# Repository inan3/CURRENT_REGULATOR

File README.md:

PCB Module based on STM32G491RET6 acting as a water sensor just for tests purposes. Nominal working voltage is 12V.
It is designed to receive commands either by UART or LIN-BUS containing info about:
  1. How many voltage between 0-3.3V to put in a connector A. 
     DAC_OUT1 from the STM32 is used for this purpose.
  2. How many current between 0-20mA to put in a connector B.
     DAC_OUT2 from the STM32 is used for this purpose. An equivalent voltage is generated from the DAC that will go through a phase of voltage-current conversion with the Improved Howland Current Pump achieving an outside current from 0mA to 20mA with 0V-3.3V.
  3. Toggle between 0V & 12V that must reach a connector C.
     This phase is achieved with high side switching topology to toggle 4 different pins of 2 separate connectores to toggle between 0V and 12V.

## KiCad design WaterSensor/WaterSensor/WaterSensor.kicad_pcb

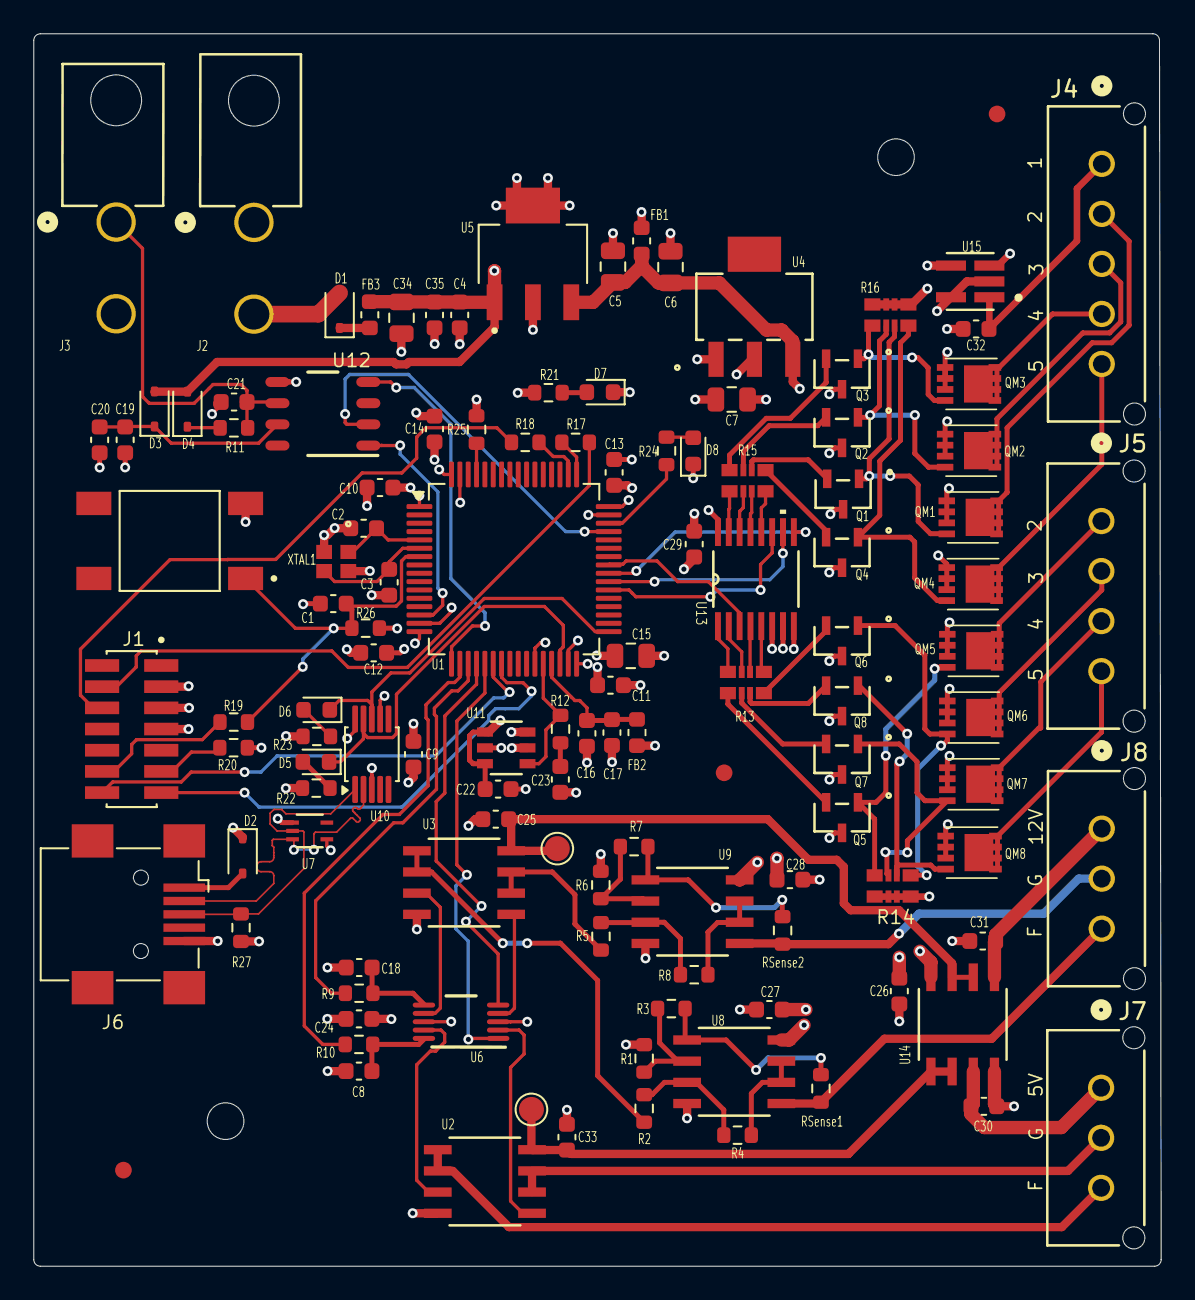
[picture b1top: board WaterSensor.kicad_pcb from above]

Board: 4 copper layers, 67.6 x 73.9 mm, 123 parts (0 on the bottom side), 104 nets.

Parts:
C1, C24, C25, C26, C27, C28, C29, C30, C31, C32, C33: 0.1uF; C_0603_1608Metric
C2, C3: 8.2pF; C_0603_1608Metric
C4: 0.22uF; C_0603_1608Metric
C5, C6, C7, C34: 10uF; C_0805_2012Metric
C8, C18: 10nF; C_0603_1608Metric
C9, C17, C20: 1uF; C_0603_1608Metric
C10, C11, C12, C13, C14, C16, C19, C35: 100nF; C_0603_1608Metric
C15: 4.7uF; C_0805_2012Metric
C21: 1nF; C_0603_1608Metric
C22, C23: 2.2uF; C_0603_1608Metric
D1, D2, D3, D4: 1N5819WS; D_SOD-323
D5: Yellow; LED_0603_1608Metric
D6: Green; LED_0603_1608Metric
D7: Red; LED_0603_1608Metric
D8: Blue; LED_0603_1608Metric
FB1, FB3: HI1206N101R-10; L_0603_1608Metric
FB2: HZ0603C601R-10; L_0603_1608Metric
FID1, FID2, FID3: Fiducial; Fiducial_1mm_Mask2mm
H1, H2: MountingHole; MountingHole_2.2mm_M2
J1: ST-LINK; Connector_IDC_02x07_1_27mm_SMD
J2: PS_IN; Conn_1x2_MiniFit_1724480002
J3: LIN; Conn_1x2_MiniFit_1724480002
J4: BLK8C; Conn_1x5_MicroFit_436500527
J5: BLK9C; Conn_1x4_MicroFit_0436500427
J6: USB_B_Mini; USB_Mini-B_Wuerth_65100516121_Horizontal
J7: BLKA; Conn_1x3_MicroFit_436500327
J8: BLKB; Conn_1x3_MicroFit_436500327
Q1, Q2, Q3, Q4, Q5, Q6, Q7, Q8: BC848BLT1G; SOT-23_ONS-L
QM1, QM2, QM3, QM4, QM5, QM6, QM7, QM8: PMOS; LIB-SIS862DNT1GE3
R1, R2, R3, R4, R5, R6, R7, R8: 100k; R_0603_1608Metric
R9, R10, R11: 1k; R_0603_1608Metric
R12: 50; R_0603_1608Metric
R13, R14, R15, R16: EXB-28V220JX; EXB28V_PAN
R17, R18, R19: 22; R_0603_1608Metric
R20: 100; R_0603_1608Metric
R21, R22: 220; R_0603_1608Metric
R23, R24: 120; R_0603_1608Metric
R25, R26: 10k; R_0603_1608Metric
R27: 1k5; R_0603_1608Metric
RSense1, RSense2: 165; R_0603_1608Metric
SW1: SW_Push; SW_TS04-66-43-BK-160-SMT
TP1: TP1; TestPoint_Pad_D1.5mm
TP2: TP2; TestPoint_Pad_D1.5mm
U1: STM32G491RET6; LQFP-64_10x10mm_P0.5mm
U2, U3, U8, U9, U14: OPA2990IDR; D8_TEX-M
U4: LM1117MP-3.3; SOT223-318H_OSI-M
U5: LM7805MPX/NOPB; LM7805MPX_NOPB
U6: TS5A23157QDGSRQ1; DGS0010A_N
U7: TPD2E001DRLR; DRL5-M
U10: CH340E; MSOP-10_3x3mm_P0.5mm
U11: MCP1501T-33E/CHY; SOT-23-6_CHY_MCH
U12: TLIN1029DRQ1; D0008A_N
U13: SN74LV4051APWR; PW16
U15: OPA990IDBVR; DBV0005A-IPC_A
XTAL1: FA-128 24.0000MB-W0; FA-128_2x1p6_SEC

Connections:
+3.3V: C7.1, C9.1, C10.1, C11.1, C12.1, C13.1, C14.1, C15.1, C22.1, C29.1, FB2.1, J1.3, R21.1, R22.1, R23.1, R26.1, R27.1, U1.1 (VBAT), U1.16 (VDD), U1.32 (VDD), U1.48 (VDD), U1.64 (VDD), U4.2 (VO), U10.7 (VCC), U10.10 (V3), U11.4 (*SHDN), U11.6 (VDD), U13.16 (VCC)
+5V: C5.1, C6.1, C24.1, FB1.2, U4.3 (VI), U5.3 (OUTPUT), U6.8 (V+), U7.4 (VCC)
+12V: QM1.3 (S), QM2.3 (S), QM3.3 (S), QM4.3 (S), QM5.3 (S), QM6.3 (S), QM7.3 (S), QM8.3 (S), R14.5, R14.6, R14.7, R14.8, R16.5, R16.6, R16.7, R16.8, U15.2 (-), U15.5
/BLK-C-Water/+12V_BLK8C-2: J4.2, QM1.1 (D)
/BLK-C-Water/+12V_BLK8C-3: J4.3, QM2.1 (D)
/BLK-C-Water/+12V_BLK8C-4: J4.4, QM3.1 (D)
/BLK-C-Water/+12V_BLK8C-5: J4.5, QM4.1 (D)
/BLK-C-Water/+12V_BLK9C-2: J5.1, QM5.1 (D)
/BLK-C-Water/+12V_BLK9C-3: J5.2, QM6.1 (D)
/BLK-C-Water/+12V_BLK9C-4: J5.3, QM7.1 (D)
/BLK-C-Water/+12V_BLK9C-5: J5.4, QM8.1 (D)
/BLK-C-Water/BLKC_PWR: C32.1, J4.1, U15.1 (+)
/DAC_PROT&SWITCH/BLKA_PWR: C30.1, J7.1, U14.3 (In1+)
/DAC_PROT&SWITCH/BLKA_PWR_BUFF: C33.1, TP1.1, U2.8 (VCC+), U14.1 (Out1), U14.2 (In1-)
/DAC_PROT&SWITCH/BLKB_PWR: C31.1, J8.1, U14.5 (In2+)
/DAC_PROT&SWITCH/BLKB_PWR_BUFF: C25.1, TP2.1, U3.8 (VCC+), U14.6 (In2-), U14.7 (Out2)
/DAC_PROT&SWITCH/DAC_A_IN1+: U2.3 (In1+), U6.9 (NC1)
/DAC_PROT&SWITCH/DAC_A_IN2+: U2.5 (In2+), U6.2 (NO1)
/DAC_PROT&SWITCH/DAC_A_RAW_F: C8.2, R10.2, U6.10 (COM1)
/DAC_PROT&SWITCH/DAC_B_IN1+: U3.3 (In1+), U6.7 (NC2)
/DAC_PROT&SWITCH/DAC_B_IN2+: U3.5 (In2+), U6.4 (NO2)
/DAC_PROT&SWITCH/DAC_B_RAW_F: C18.1, R9.2, U6.6 (COM2)
/DAC_PROT&SWITCH/FW_DAC_IN_A: J7.3, U2.1 (Out1), U2.2 (In1-)
/DAC_PROT&SWITCH/GW_DAC_IN_A: J7.2, U2.6 (In2-), U2.7 (Out2)
/LIN_BUS: C21.1, J3.1, R11.2, U12.6 (LIN)
/USB_D+: J6.3 (D+), R27.2, U7.2 (IO1), U10.1 (UD+)
/USB_D-: J6.2 (D-), U7.3 (IO2), U10.2 (UD-)
/VIConverter/FW_DAC_IN_B_IN1-: R1.2, R3.1, U8.2 (In1-)
/VIConverter/FW_OUT2: R4.1, U8.6 (In2-), U8.7 (Out2)
/VIConverter/GW_DAC_IN_B_IN1-: R6.2, R7.1, U9.2 (In1-)
/VIConverter/GW_OUT2: R8.1, U9.6 (In2-), U9.7 (Out2)
/VIConverter/IoutFW: J8.3, RSense1.1, U8.5 (In2+)
/VIConverter/IoutGW: J8.2, RSense2.1, U9.5 (In2+)
BLKC_CTRL_IN: U1.41 (PC9), U13.3 (COM)
BLKC_SEL_A: U1.38 (PC6), U13.11 (A)
BLKC_SEL_B: U1.39 (PC7), U13.10 (B)
BLKC_SEL_C: U1.40 (PC8), U13.9 (C)
BOOT: R25.1, U1.61 (PB8)
DAC_IN_A: R10.1, U1.18 (PA4)
DAC_IN_B: R9.1, U1.19 (PA5)
EN_LIN: U1.45 (PA11), U12.2 (EN)
FW_DAC_IN_B: R2.1, U3.1 (Out1), U3.2 (In1-)
GND: C1.2, C2.2, C3.2, C4.2, C5.2, C6.2, C7.2, C8.1, C9.2, C10.2, C11.2, C12.2, C13.2, C14.2, C15.2, C16.2, C17.2, C18.2, C19.2, C20.2, C21.2, C22.2, C23.2, C24.2, C25.2, C26.2, C27.2, C28.2, C29.2, C30.2, C31.2, C32.2, C33.2, C34.2, C35.2, D7.1 (K), D8.1 (K), J1.5, J1.7, J2.1, J3.2, J6.5 (GND), Q1.3 (E), Q2.3 (E), Q3.3 (E), Q4.3 (E), Q5.3 (E), Q6.3 (E), Q7.3 (E), Q8.3 (E), R1.1, R6.1, R20.1, R25.2, SW1.2, U1.15 (VSS), U1.27 (VSSA), U1.31 (VSS), U1.47 (VSS), U1.63 (VSS), U2.4 (VCC-), U3.4 (VCC-), U4.1 (GND), U5.2 (GND), U5.4 (GND), U6.3 (GND), U7.1 (GND), U8.4 (VCC-), U9.4 (VCC-), U10.3 (GND), U11.2 (GND), U11.3 (GND), U11.5 (GND), U12.5 (GND), U13.6 (INH), U13.7 (GND), U13.8 (GND), U14.4 (VCC-), U15.4 (V-), XTAL1.2, XTAL1.4
GW_DAC_IN_B: R5.1, U3.6 (In2-), U3.7 (Out2)
IN_A: U1.21 (PA7), U6.1 (IN1)
IN_B: U1.20 (PA6), U6.5 (IN2)
In1+: R2.2, R4.2, U8.3 (In1+)
NRST: C1.1, R19.2, R26.2, SW1.1, U1.7 (PG10)
unnamed: C23.1, R12.2
unnamed: D1.1 (K), FB3.1
unnamed: D2.2 (A), J6.1 (VBUS)
unnamed: C19.1, C20.1, D3.1 (K), U12.7 (VSUP)
unnamed: D4.1 (K), R11.1
unnamed: D5.2 (A), R22.2
unnamed: D6.2 (A), R23.2
unnamed: D7.2 (A), R21.2
unnamed: D8.2 (A), R24.2
unnamed: J1.4, R17.1
unnamed: J1.6, R18.1
unnamed: J1.11, R20.2
unnamed: J1.12, R19.1
unnamed: Q1.2 (B), R15.6
unnamed: Q1.1 (C), QM1.2 (G), R16.3
unnamed: Q2.2 (B), R15.7
unnamed: Q2.1 (C), QM2.2 (G), R16.2
unnamed: Q3.2 (B), R15.8
unnamed: Q3.1 (C), QM3.2 (G), R16.1
unnamed: Q4.2 (B), R15.5
unnamed: Q4.1 (C), QM4.2 (G), R16.4
unnamed: Q5.2 (B), R13.5
unnamed: Q5.1 (C), QM5.2 (G), R14.4
unnamed: Q6.2 (B), R13.8
unnamed: Q6.1 (C), QM6.2 (G), R14.1
unnamed: Q7.2 (B), R13.6
unnamed: Q7.1 (C), QM7.2 (G), R14.3
unnamed: Q8.2 (B), R13.7
unnamed: Q8.1 (C), QM8.2 (G), R14.2
unnamed: R15.3, U13.13 (Y0)
unnamed: R15.2, U13.14 (Y1)
unnamed: R15.1, U13.15 (Y2)
unnamed: R15.4, U13.12 (Y3)
unnamed: R13.4, U13.1 (Y4)
unnamed: R13.1, U13.5 (Y5)
unnamed: R13.3, U13.2 (Y6)
unnamed: R13.2, U13.4 (Y7)
O2In1+: R5.2, R8.2, U9.3 (In1+)
O2Out1: R7.2, RSense2.2, U9.1 (Out1)
OSC_IN: C2.1, U1.5 (PF0), XTAL1.1
OSC_OUT: C3.1, U1.6 (PF1), XTAL1.3
Out1: R3.2, RSense1.2, U8.1 (Out1)
PS_IN: D1.2 (A), J2.2
PS_RAW: C4.1, C26.1, C27.1, C28.1, C34.1, C35.1, D3.2 (A), D4.2 (A), FB3.2, U5.1 (INPUT), U8.8 (VCC+), U9.8 (VCC+), U14.8 (VCC+), U15.3 (V+)
SWCLK: R18.2, U1.50 (PA14)
SWDIO: R17.2, U1.49 (PA13)
USART1_RX: J1.13, U1.23 (PC5)
USART1_TX: J1.14, U1.22 (PC4)
USART2_RX: U1.17 (PA3), U12.4 (TXD)
USART2_TX: U1.14 (PA2), U12.1 (RXD)
USART3_RX: D6.1 (K), U1.33 (PB11), U10.8 (TXD)
USART3_TX: D5.1 (K), U1.30 (PB10), U10.9 (RXD)
VDDA: C16.1, C17.1, FB2.2, U1.29 (VDDA)
VREF+: R12.1, U1.28 (VREF+), U11.1 (OUT)
Vdrive: D2.1 (K), FB1.1
uC_Alive: R24.1, U1.46 (PA12)

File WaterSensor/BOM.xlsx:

Reference | Manufacturer P/N | JLCPCB P/N | Value | Manufacturer
C1 | CC0603JRX7R9BB104 | C91183 | 100nF 50V X7R ±5% 0603 | YAGEO
C2, C3 | CC0603CRNPO9BN8R2 | C277519 | 50V 8.2pF NP0 0603 | YAGEO
C4 | CC0603JRX7R9BB224 | C519575 | 220nF 50V X7R ±5% 0603 | YAGEO
C5, C6, C7 | CC0603KRX5R5BB106 | C109455 | 10uF 6.3V X5R ±10% | YAGEO
C8, C18 | CC0603JRX7R9BB103 | C115056 | 10nF 50V X7R ±5% 0603 | YAGEO
C9, C17, C20 | CC0603KRX5R9BB105 | C128624 | 1uF 50V X5R ±10% 0603 | YAGEO
C10, C11, C12, C13, C14, C16, C19, C35 | CC0603JRX7R9BB104 | C91183 | 100nF 50V X7R ±5% 0603 | YAGEO
C15 | CC0603KRX5R8BB475 | C326580 | 25V 4.7uF X5R ±10% 0603 | YAGEO
C21 | CC0603JRNPO9BN102 | C106246 | 1nF 50V NP0 ±5% 0603 | YAGEO
C22, C23 | CC0603KRX5R8BB225 | C309478 | 2.2uF 25V X5R ±10% 0603 | YAGEO
C24, C25, C26, C27, C28, C29, C30, C31, C32, C33 | CC0603JRX7R9BB104 | C91183 | 100nF 50V X7R ±5% 0603 | YAGEO
C34 | CC0805KKX5R7BB106 | C89827 | 10uF 16V X5R ±10% 0805 Multilayer Ceramic Capacitors MLCC - SMD/SMT ROHS | YAGEO
D1 | 1N5819WS | C191023 | 1 Independent 1A 25A 40V 500uA@40V 600mV@1A SOD-323 Schottky Diodes ROHS | Guangdong Hottech
D2 | 1N5819WS | C191023 | 1 Independent 1A 25A 40V 500uA@40V 600mV@1A SOD-323 Schottky Diodes ROHS | Guangdong Hottech
D3 | 1N5819WS | C191023 | 1 Independent 1A 25A 40V 500uA@40V 600mV@1A SOD-323 Schottky Diodes ROHS | Guangdong Hottech
D4 | 1N5819WS | C191023 | 1 Independent 1A 25A 40V 500uA@40V 600mV@1A SOD-323 Schottky Diodes ROHS | Guangdong Hottech
D5 | XL-1608UYC-06 | C965802 | Yellow LED | XingLight
D6 | XL-1608UGC-04 | C965804 | Green LED | XingLight
D7 | XL-1608SURC-06 | C965799 | Red LED | XingLight
D8 | XL-1608UBC-04 | C965807 | Blue LED | XingLight
FB1, FB3 | BLM18EG101TN1D | C76893 | -55℃~+125℃ 1 100Ω@100MHz 2A 45mΩ ±25% 0603 Ferrite Beads ROHS | Murata Electronics
FB2 | BLM18AG601SH1D | C73225 | -55℃~+125℃ 1 380mΩ 500mA 600Ω@100MHz ±25% 0603 Ferrite Beads ROHS | Murata Electronics
J1 | 20021321-00014C1LF | C3319516 | -40℃~+105℃ 1.27mm 1.27mm 14P 2 4.5mm Phosphor bronze Square Hole Surface Mount,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 | Amphenol ICC
J2, J3, J7, J8 | 1724480002 | C5188718 | -40℃~+105℃ 1 13A 2 2P 2x1P 4.2mm 4.2mm 600V Black Brass PA Right Angle Tin UL94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 | Molex
J4 | 436500427 | C563850 | -40℃~+105℃ 1 18.65mm 1x5P 3mm 5 5.57mm 5P 600V 8.5A 9.9mm Black Brass Micro-Fit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 | Molex
J5 | 436500527 | C19183988 | -40℃~+105℃ 1 15.65mm 1x4P 3mm 4 4P 600V 8.5A Black Brass Through Hole Tin UL94V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 | Molex
J6 | 65100516121 | C5120592 | -40℃~+105℃ 1 1A 30V 5P Black Female Mini-B Surface Mount, Right Angle USB 2.0 S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 | Würth Elektronik
Q1, Q2, Q3, Q4, Q5, Q6, Q7, Q8 | BC848BLT1G | C163725 | -55℃~+150℃ 1 NPN 100MHz 100mA 110 225mW 250mV 30V 5V 5uA NPN SOT-23 Bipolar (BJ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 | Onsemi
QM1, QM2, QM3, QM4, QM5, QM6, QM7, QM8 | SIS427EDN-T1-GE3 | C727478 | -55℃~+150℃ 1 P-Channel 1.2V 1.93nF 10.6mΩ@10V 15A 3.7W、52W 30V 66nC@10V PowerPA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 | Vishay Intertech
R1, R2, R3, R4, R5, R6, R7, R8 | CRT0603-BY-1003ELF | C4332041 | -55℃~+155℃ 100kΩ 100mW Thin Film Resistor ±0.1% ±25ppm/℃ 0603 Chip Resistor - S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 | Bourns Inc.
R9, R10, R11 | RS-03K1001FT | C115325 | -55℃~+155℃ 100mW 1kΩ 50V Thick Film Resistor ±1% ±100ppm/℃ 0603 Chip Resistor -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 | FH (Guangdong Fenghua Advanced Tech)
R12 | RT0603BRE0750RL | C849792 | RES SMD 50 OHM 0.1% 1/10W 0603 | YAGEO
R13, R14, R15, R16 | EXB-28V220JX | C2649457 | 22Ω 4 63mW 8 ±200ppm/℃ ±5% 0402x4 Resistor Networks, Arrays ROHS | Panasonic Electronic Components
R17, R18, R19 | CR0603-FX-22R0ELF | C203424 | RES SMD 22 OHM 1% 1/10W 0603 | Bourns Inc.
R20 | CR0603-FX-1000ELF | C203215 | RES SMD 100 OHM 1% 1/10W 0603 | Bourns Inc.
R21, R22 | CR0603-FX-2200ELF | C203410 | RES SMD 220 OHM 1% 1/10W 0603 | Bourns Inc.
R23, R24 | CR0603-FX-1200ELF | C203262 | RES SMD 120 OHM 1% 1/10W 0603 | Bourns Inc.
R25, R26 | CR0603-FX-1002ELF | C840630 | RES SMD 10K OHM 1% 1/10W 0603 | Bourns Inc.
R27 | CRCW06031K50FKEAC | C844332 | RES 1.5K OHM 1% 1/10W 0603 | Vishay Dale
RSense1, RSense2 | RT0603BRD07165RL | C861151 | -55℃~+155℃ 100mW 165Ω 75V Thin Film Resistor ±0.1% ±25ppm/℃ 0603 Chip Resistor 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 | YAGEO
SW1 | TS04-66-43-BK-160-SMT | C4364498 | Switch | Same Sky (Formerly CUI Devices)
U1 | STM32G491RET6 | C3231005 | IC MCU 32BIT 512KB FLASH 64LQFP | STMicroelectronics
U2, U3, U8, U9, U14 | OPA2990IDR | C2058283 | IC OPAMP GP 2 CIRCUIT 8SOIC | Texas Instruments
U4 | LM1117MPX-3.3/NOPB | C9662 | IC REG LIN 3.3V 800MA SOT-223-4 | Texas Instruments
U5 | LM7805MPX/NOPB | C2848241 | IC REG LINEAR 5V 1.5A SOT-223-4 | Texas Instruments
U6 | TS5A23157QDGSRQ1 | C523778 | IC SWITCH SPDT X 2 15OHM 10VSSOP | Texas Instruments
U7 | TPD2E001DRLR | C150526 | TVS DIODE 5.5VWM SOT5 | Texas Instruments
U10 | CH340E | C99652 | USB/UART
U11 | MCP1501T-33E/CHY | C2156758 | IC VREF SERIES 3.3V SOT23-6 | Microchip Technology
U12 | TLIN1029DRQ1 | C190544 | Transceptor 1/1 LINbus 8-SOIC | Texas Instruments
U13 | SN74LV4051APWR | C7793 | IC MUX 8:1 75OHM 16TSSOP | Texas Instruments
U15 | OPA990IDBVR | C1855809 | -20V~-1.35V、1.35V~20V -40℃~+125℃ 1 1.1MHz 10pA 115dB 120uA 2.7V~40V 300uV 30nV/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 | Texas Instruments
XTAL1 | FA-128 24.0000MB-W | C2449805 | CRYSTAL 24.0000MHZ 12PF SMD | ECS

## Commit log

2026-01-07 first commit of water sensor design
2026-01-10 schematic done
2026-01-12 faltan pines para bloque C
2026-02-17 ready to manufacture
2026-02-17 Add PCB module description to README
    Added description of PCB module functionality and specifications.
